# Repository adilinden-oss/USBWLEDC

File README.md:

# USBWLEDC
USB Sound Reactive WLED Controller

## Why This Fork?

This is my fork of the [NandXor96/USBWLEDC](https://github.com/NandXor96/USBWLEDC) WLED Controller.  There is a [Reddit post](https://www.reddit.com/r/WLED/comments/1c1dhp0/comment/kz3xn8g/?utm_source=share&utm_medium=web3x&utm_name=web3xcss&utm_term=1&utm_content=share_button) explaining how to order the (mostly) assembled board from JLCPCB.  Unfortunately, when I went to order it turned out that neither the **GSA4737** nor the (pin compatible?) **SPM1423** were available. Checking parts sources, they appear to be obsolete at this point.  I redesigned the board to support the **ICS-43434** instead, which is a current stocked part (albeit more expensive!).

The included production files were created with KiCAD v8.0.7 and exported using the [KiCAD JLCPCB Tools Plugin](https://github.com/Bouni/kicad-jlcpcb-tools).

## Features

- USB-C for flashing and power (max. 3A)
- Small size (30mm x 35mm)
- Cheap components
- GSA4737 MEMS Microphone (similar to SPM1423)
- Solder Pads instead of Screw Terminal Blocks
- Files for panelized version (4x4)
- Files for 3D printed case
- Front side can be populated by JLCPCB

## In Action

Here are two brief video clips of WLED with audio reactive enabled on this board.

## Case

## Entering Flash Mode

To enter the Flash mode of the USBWLEDC, simply hold down the button as you connect the USB cable to a computer.

## WLED Config

| Name | Value |
|------|-------|
| LED Output 1: GPIO | 32 |
| LED Output 2: GPIO | 33 |
| Button 0: GPIO | 0 |
| Digitalmic: Type | Generic I2S |
| Digitalmic: Pin I2S SD  | GPIO 22 |
| Digitalmic: Pin I2S WS  | GPIO 23 |
| Digitalmic: Pin I2S SCK | GPIO 21 |

## BOM

|Designators   |Footprint                                       |Quantity|Value                  |LCSC Part #|
|--------------|------------------------------------------------|--------|-----------------------|-----------|
|C1*, C2, C4|Capacitor_SMD:C_0603_1608Metric                           |3    |100nF                  |C14663  |
|C3, C5, C7 |Capacitor_SMD:C_0805_2012Metric                           |3    |10uF                   |C15850  |
|C6         |Capacitor_SMD:C_0603_1608Metric                           |1    |1uF                    |C15849  |
|C8         |Capacitor_SMD:CP_Elec_5x5.4                               |1    |100uF                  |C96182  |
|J10        |Connector_USB:USB_C_Receptacle_G-Switch_GT-USB-7010ASV    |1    |USB-C Receptacle       |C2988369|
|MK1*       |InvenSense_ICS-43434-6_3.5x2.65mm                         |1    |ICS-43434 MEMS Mic     |C2988369|
|R1*        |Resistor_SMD:R_0603_1608Metric                            |1    |100k                   |C25803  |
|R2, R3     |Resistor_SMD:R_0603_1608Metric                            |2    |10k                    |C25804  |
|R4, R5     |Resistor_SMD:R_0603_1608Metric                            |2    |5.1k                   |C23186  |
|SW1        |Button_Switch_SMD:SW_Push_1P1T_XKB_TS-1187A               |1    |Push Button Flash      |C318884 |
|U1         |Package_SO:SOP-8_3.9x4.9mm_P1.27mm                        |1    |CH340N                 |C2977777|
|U2         |Package_TO_SOT_SMD:SOT-223-3_TabPin2                      |1    |AMS1117-3.3            |C6186   |
|U3**       |RF_Module:ESP32-WROOM-32                                  |1    |ESP32-WROOM-32         |C701341 |

\* You can build it without the microphone. Then you don't need R1, C1 and MK1.

\*\* The ESP32-WROOM Module can be purchased at a lower cost on AliExpress.

## Assembly

When ordering from JLCPCB, you have the option to get the front side of the board pre-populated - A service I strongly endorse. Subsequently, you'll only need to solder the ESP32-WROOM module onto the reverse side. With sufficient flux, this task can be accomplished with relative ease.

For those looking to populate the whole board, I suggest using a hot plate or a reflow oven for the front side.

    Be careful to keep Isopropyl Alcohol away from the hole of the microphone when cleaning the board!

## Disclaimer

The circuit board provided on this GitHub repository is offered "as is," without any warranties or guarantees of any kind. By accessing and utilizing this circuit board, you acknowledge and agree that you do so at your own risk.

The creator and contributor of this repository, shall not be held responsible or liable for any damages, losses, or injuries that may occur as a result of building and / or using this circuit board. This includes but is not limited to any direct, indirect, consequential, or incidental damages.

Electricity is dangerous. Only attempt this project if you know what you're doing.

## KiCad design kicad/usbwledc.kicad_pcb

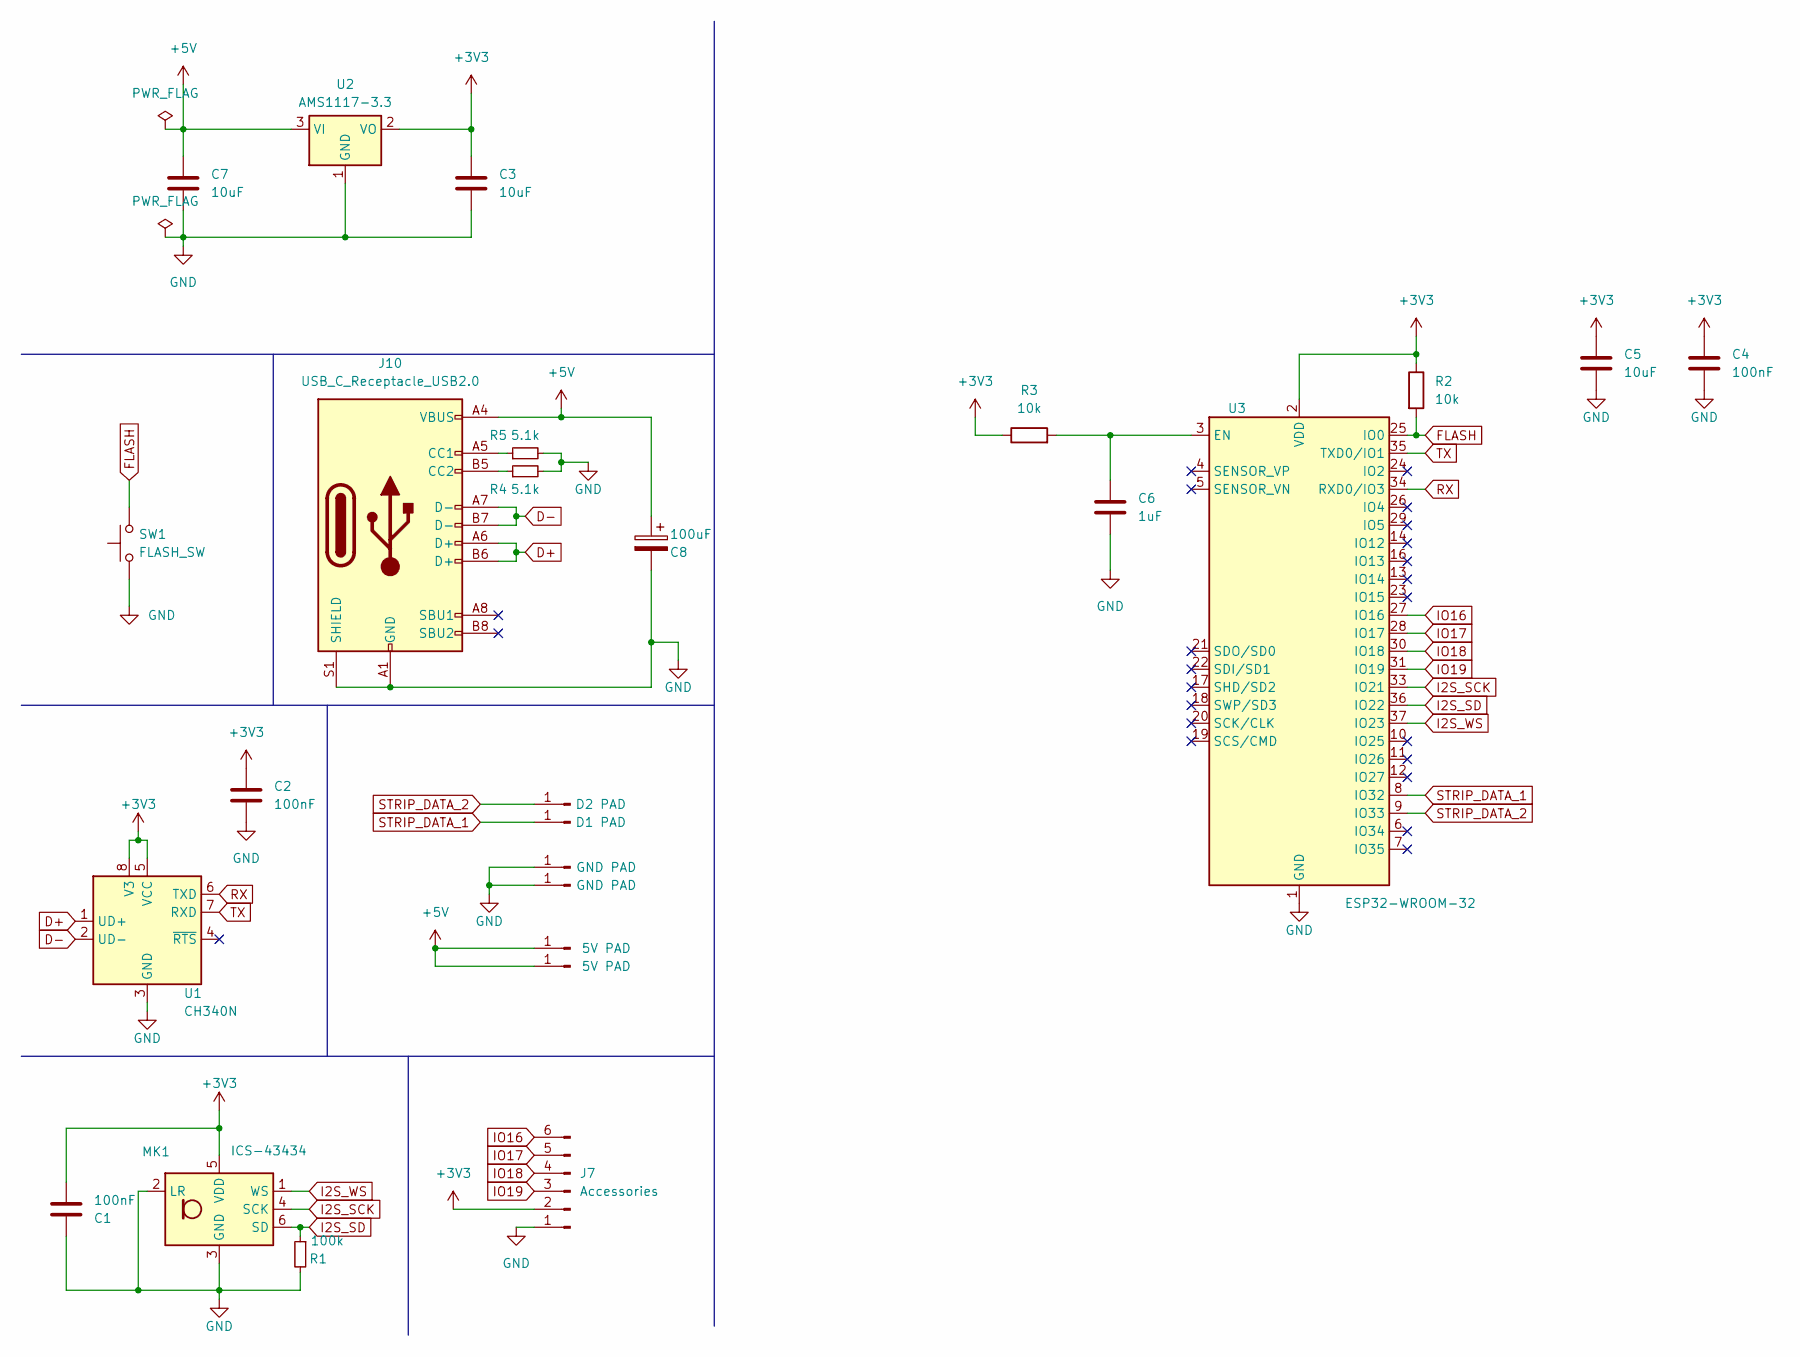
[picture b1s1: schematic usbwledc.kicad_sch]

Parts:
C1, C2, C4: 100nF; C_0603_1608Metric; MPN C14663; LCSC C14663
C3, C5, C7: 10uF; C_0805_2012Metric; MPN C15850; LCSC C15850
C6: 1uF; C_0603_1608Metric; MPN C15849; LCSC C15849
C8: 100uF; CP_Elec_5x5.4; MPN C131115; LCSC C96182
J1, J4: 5V PAD; SolderWirePad_1x01_SMD_3x6mm
J2: D1 PAD; SolderWirePad_1x01_SMD_3x6mm
J3, J6: GND PAD; SolderWirePad_1x01_SMD_3x6mm
J5: D2 PAD; SolderWirePad_1x01_SMD_3x6mm
J7: Accessories; PinHeader_1x06_P2.54mm_Vertical
J10: USB_C_Receptacle_USB2.0; USB_C_Receptacle_G-Switch_GT-USB-7010ASV; MPN C2988369; LCSC C2988369
MK1: ICS-43434; InvenSense_ICS-43434-6_3.5x2.65mm; LCSC C5656610
R1: 100k; R_0603_1608Metric; MPN C25803; LCSC C25803
R2, R3: 10k; R_0603_1608Metric; MPN C25804; LCSC C25804
R4, R5: 5.1k; R_0603_1608Metric; MPN C23186; LCSC C23186
SW1: FLASH_SW; SW_Push_1P1T_XKB_TS-1187A; MPN C318884; LCSC C318884
U1: CH340N; SOP-8_3.9x4.9mm_P1.27mm; MPN C2977777; LCSC C2977777
U2: AMS1117-3.3; SOT-223-3_TabPin2; MPN C6186; LCSC C6186
U3: ESP32-WROOM-32; MPN C701341; Mouser 356-ESP32WRM32E132PH

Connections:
+3V3: C1.2, C2.2, C3.1, C4.2, C5.1, J7.2, MK1.5 (VDD), R2.1, R3.1, U1.5 (VCC), U1.8 (V3), U2.2 (VO), U3.2 (VDD)
+5V: C7.1, C8.1, J1.1, J4.1, J10.A4 (VBUS), J10.A9 (VBUS), J10.B4 (VBUS), J10.B9 (VBUS), U2.3 (VI)
D+: J10.A6 (D+), J10.B6 (D+), U1.1 (UD+)
D-: J10.A7 (D-), J10.B7 (D-), U1.2 (UD-)
FLASH: R2.2, SW1.2, U3.25 (IO0)
GND: C1.1, C2.1, C3.2, C4.1, C5.2, C6.2, C7.2, C8.2, J3.1, J6.1, J7.1, J10.A1 (GND), J10.A12 (GND), J10.B1 (GND), J10.B12 (GND), J10.S1 (SHIELD), MK1.2 (LR), MK1.3 (GND), R1.2, R4.2, R5.2, SW1.1, U1.3 (GND), U2.1 (GND), U3.1 (GND), U3.15 (GND), U3.38 (GND), U3.39 (GND)
I2S_SCK: MK1.4 (SCK), U3.33 (IO21)
I2S_SD: MK1.6 (SD), R1.1, U3.36 (IO22)
I2S_WS: MK1.1 (WS), U3.37 (IO23)
IO16: J7.6, U3.27 (IO16)
IO17: J7.5, U3.28 (IO17)
IO18: J7.4, U3.30 (IO18)
IO19: J7.3, U3.31 (IO19)
unnamed: J10.A5 (CC1), R5.1
unnamed: J10.B5 (CC2), R4.1
unnamed: C6.1, R3.2, U3.3 (EN)
RX: U1.6 (TXD), U3.34 (RXD0/IO3)
STRIP_DATA_1: J2.1, U3.8 (IO32)
STRIP_DATA_2: J5.1, U3.9 (IO33)
TX: U1.7 (RXD), U3.35 (TXD0/IO1)

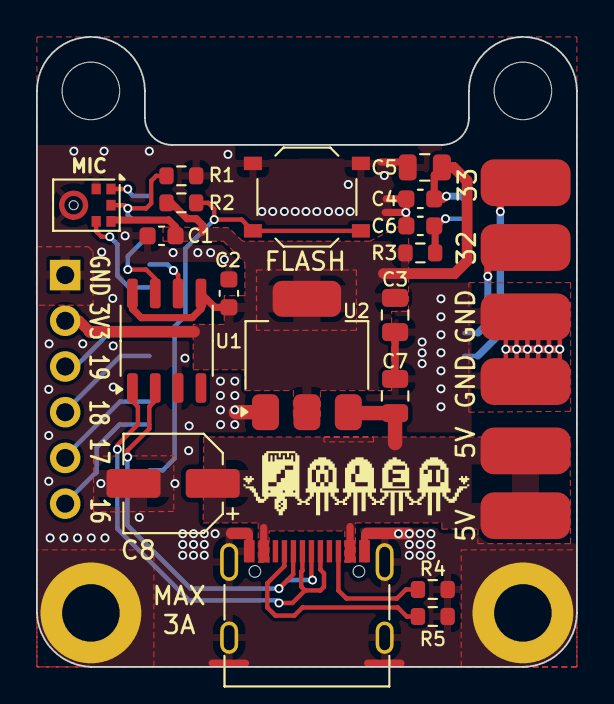
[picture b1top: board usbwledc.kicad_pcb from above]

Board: 2 copper layers, 30.0 x 35.0 mm, 30 parts (1 on the bottom side), 20 nets.

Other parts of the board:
H1, H2, H3, H4: MountingHole; MountingHole_3.2mm_M3_DIN965_Pad

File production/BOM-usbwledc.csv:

Comment,Designator,Footprint,LCSC,Quantity
100nF,"C1,C2,C4",C_0603_1608Metric,C14663,3
1uF,C6,C_0603_1608Metric,C15849,1
10uF,"C3,C5,C7",C_0805_2012Metric,C15850,3
5.1k,"R4,R5",R_0603_1608Metric,C23186,2
100k,R1,R_0603_1608Metric,C25803,1
10k,"R2,R3",R_0603_1608Metric,C25804,2
CH340N,U1,SOP-8_3.9x4.9mm_P1.27mm,C2977777,1
USB_C_Receptacle_USB2.0,J10,USB_C_Receptacle_G-Switch_GT-USB-7010ASV,C2988369,1
FLASH_SW,SW1,SW_Push_1P1T_XKB_TS-1187A,C318884,1
ICS-43434,MK1,InvenSense_ICS-43434-6_3.5x2.65mm,C5656610,1
AMS1117-3.3,U2,SOT-223-3_TabPin2,C6186,1
ESP32-WROOM-32,U3,ESP32-WROOM-32,C701341,1
100uF,C8,CP_Elec_5x5.4,C96182,1

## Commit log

2025-01-01 Replaced MEMS mic to a curent available version.
2025-01-01 Fixed URL for my branch
2025-01-03 Removed files not appropriate
2025-02-09 Added video
2025-02-09 Relative image links
2025-02-10 Added the real thing
